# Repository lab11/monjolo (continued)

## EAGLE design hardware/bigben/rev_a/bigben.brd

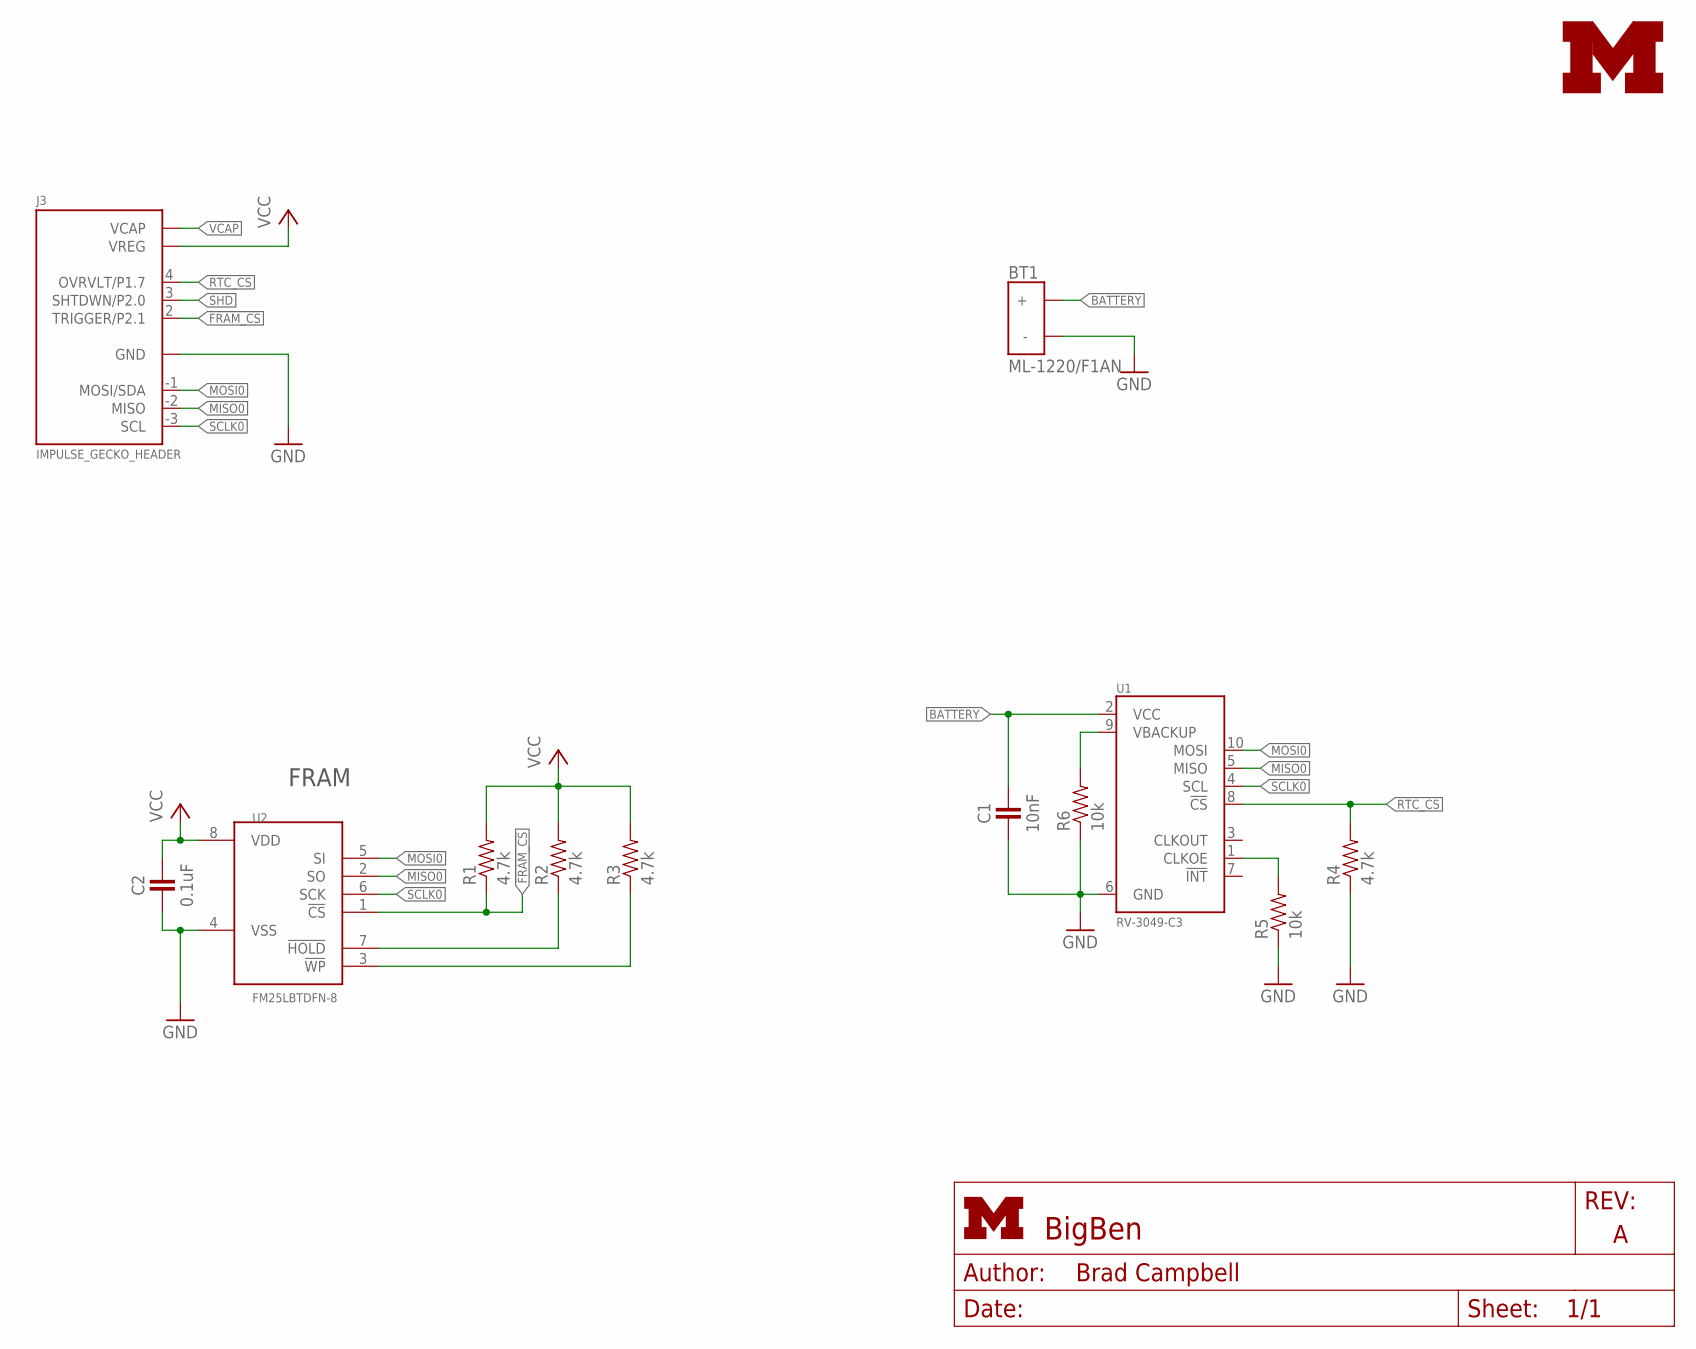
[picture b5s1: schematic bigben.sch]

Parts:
BT1: ML-1220/F1AN; ML-1220/F1BN
C1: 10nF; 0402_CAP
C2: 0.1uF; 0402_CAP
J3: IMPULSE_GECKO_HEADER; HEADER1X9/0.05IN
LOGO1: UMICH_SOLID_TINY; UMICH_SOLID_50MIL
R1, R2, R3, R4: 4.7k; 0402_RES
R5, R6: 10k; 0402_RES
U1: RV-3049-C3; MICRO-CRYSTAL-C3
U2: FM25LBTDFN-8; TDFN-8; MOUSER 877-FM25V20-DG

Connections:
!FRAM_CS: J3.2 (TRIGGER/P2.1), R1.1, U2.1 (!CS)
!FRAM_HOLD: R2.1, U2.7 (!HOLD)
!FRAM_WP: R3.1, U2.3 (!WP)
BATTERY: BT1.POS (+), C1.1, U1.2 (VCC)
GND: BT1.NEG (-), C1.2, C2.2, J3.0 (GND), R4.1, R5.1, R6.1, U1.6 (GND), U2.4 (VSS)
MISO0: J3.-2 (MISO), U1.5 (MISO), U2.2 (SO)
MOSI0: J3.-1 (MOSI/SDA), U1.10 (MOSI), U2.5 (SI)
unnamed: R6.2, U1.9 (VBACKUP)
unnamed: R5.2, U1.1 (CLKOE)
RTC_CS: J3.4 (OVRVLT/P1.7), R4.2, U1.8 (!CS)
SCLK0: J3.-3 (SCL), U1.4 (SCL), U2.6 (SCK)
SHD: J3.3 (SHTDWN/P2.0)
VCAP: J3.5 (VCAP)
VCC: C2.1, J3.1 (VREG), R1.2, R2.2, R3.2, U2.8 (VDD)

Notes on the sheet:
FRAM

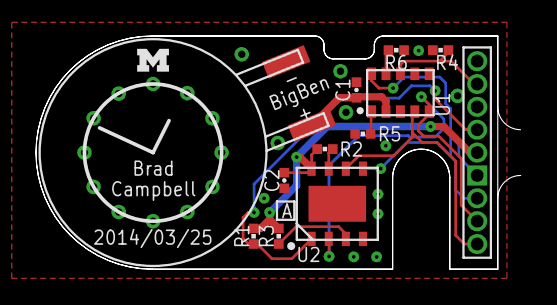
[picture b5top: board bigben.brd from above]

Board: 2 copper layers, 26.9 x 13.0 mm, 13 parts (0 on the bottom side), 12 nets.

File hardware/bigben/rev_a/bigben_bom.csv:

# Bill of Materials
# Converted from bigben_bom.xls
# Generated by bom_to_text.py

Qty,Value,Device,Package,Parts,Description,DIGIKEY,MOUSER,NEWARK
1,ML-1220/F1AN,ML-1220/F1AN,ML-1220/F1BN,BT1,BATTERY LITH 3V RECHARGE PC PINS,P663-ND,658-ML-1220/F1BN,
1,10nF,CAPACITOR,0402_CAP,C1,0402 Capacitor,445-1260-1-ND,,
1,0.1uF,CAPACITOR,0402_CAP,C2,0402 Capacitor,445-1265-1-ND,,
4,4.7k,RESISTOR,0402_RES,"R1, R2, R3, R4",Resistor,RHM4.7KCECT-ND,,
2,10k,RESISTOR,0402_RES,"R5, R6",Resistor,RHM10KCECT-ND,,
1,RV-3049-C3,RV-3049-C3,MICRO-CRYSTAL-C3,U1,The RV-3049-C3 is an ultra miniature Real-Time-Clock Module,,,RV-3049-C3
1,FM25LBTDFN-8,FM25LBTDFN-8,TDFN-8,U2,IC FRAM 4KBIT 10MHZ 8SOIC,,877-FM25V20-DG,

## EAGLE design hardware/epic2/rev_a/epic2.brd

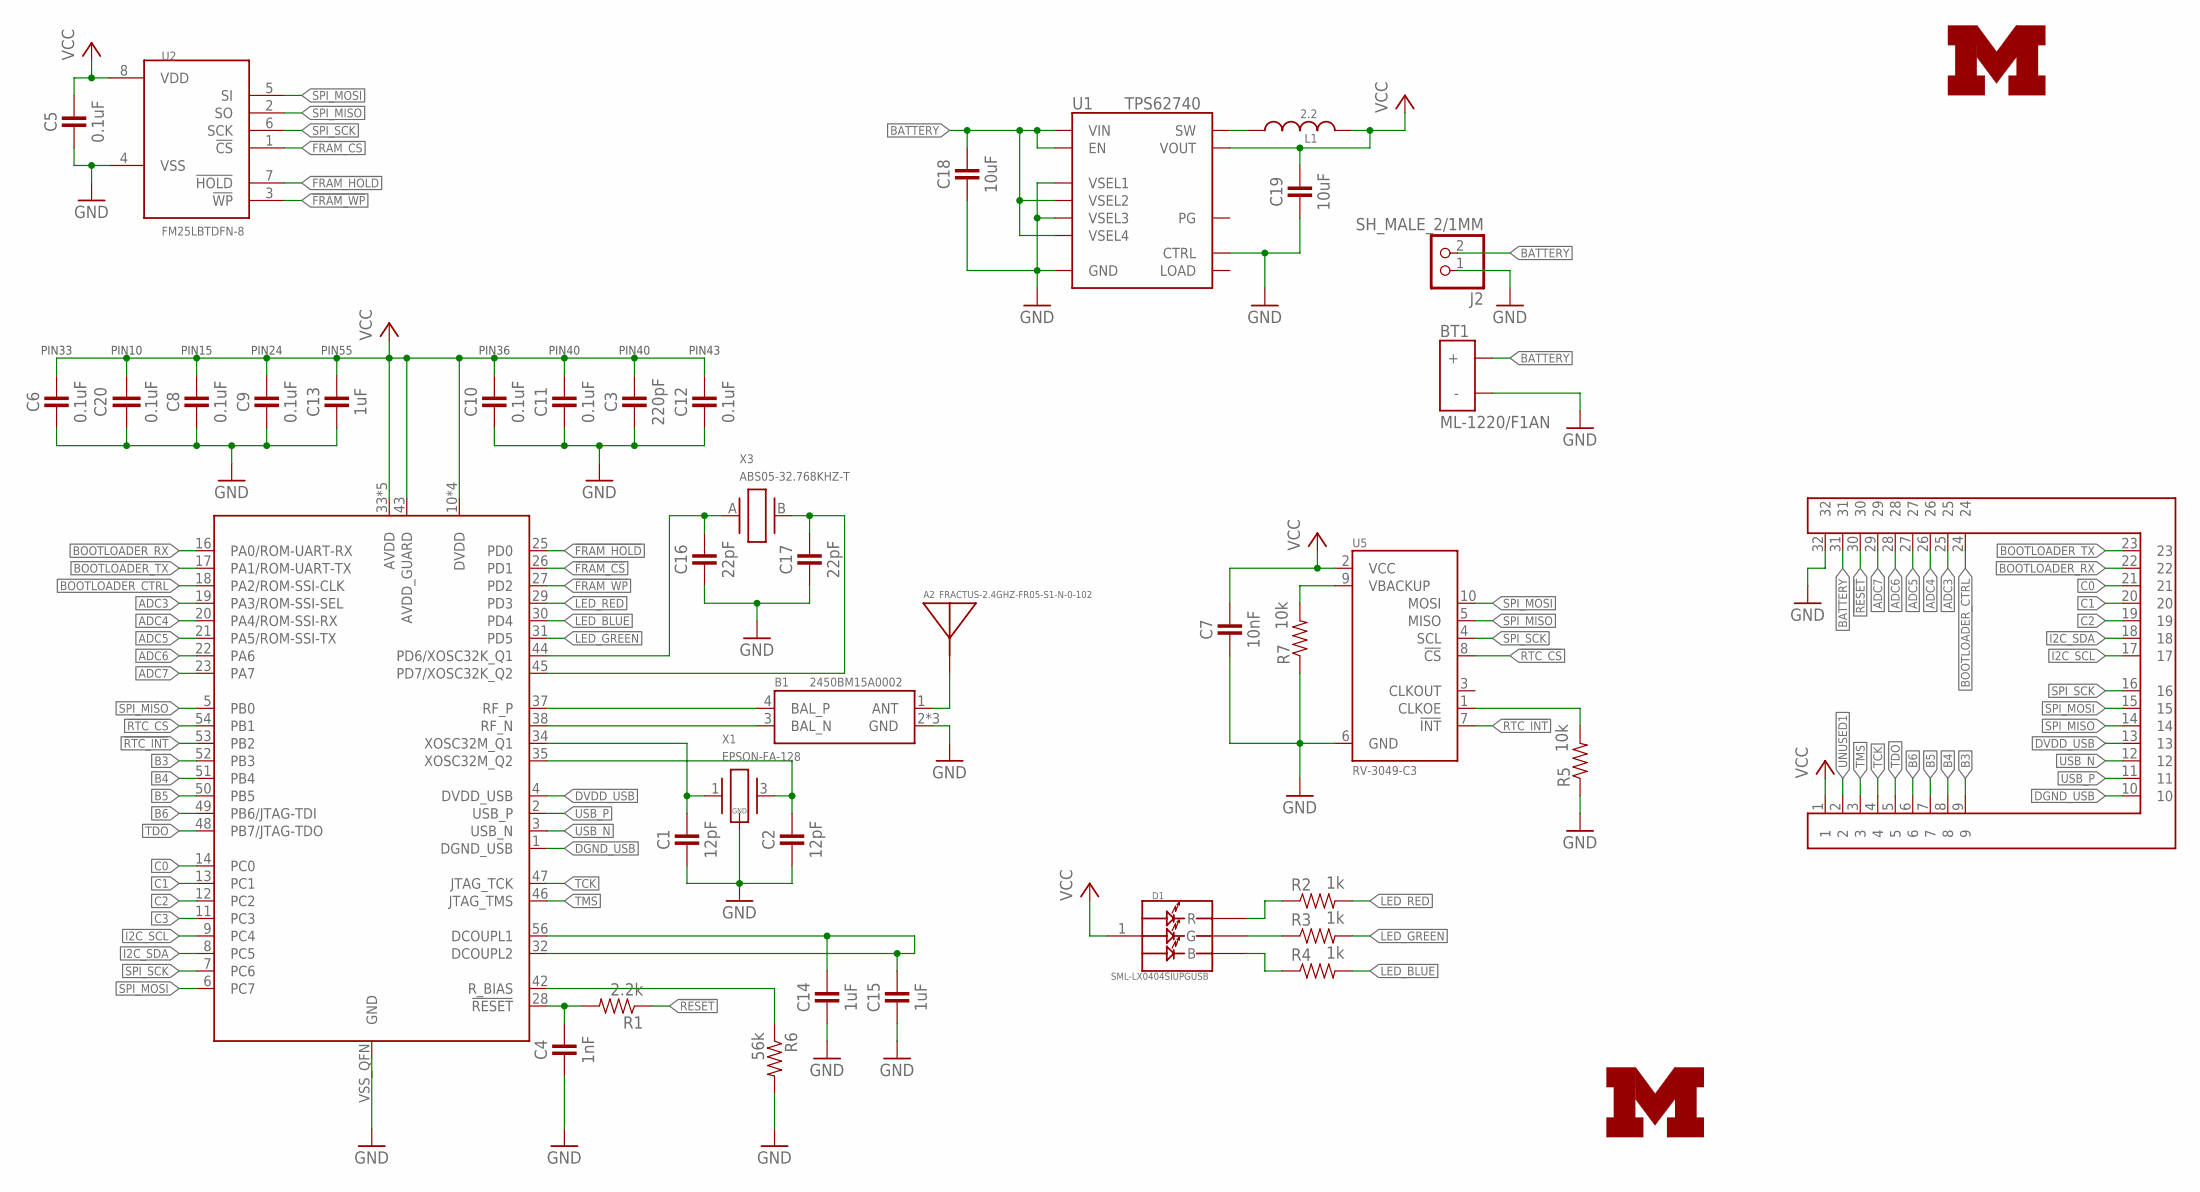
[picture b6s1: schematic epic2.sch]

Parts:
A2: FRACTUS-2.4GHZ-FR05-S1-N-0-102; FRACTUS-ANTENNA-FR05-S1-N-0-102
B1: 2450BM15A0002; 2450BM
BT1: ML-1220/F1AN; ML-1220/F1BN
C1, C2: 12pF; 0402_CAP
C3: 220pF; 0402_CAP
C4: 1nF; 0402_CAP
C5, C6, C8, C9, C10, C11, C12: 0.1uF; 0402_CAP
C7: 10nF; 0402_CAP
C13, C14, C15: 1uF; 0402_CAP
C16, C17: 22pF; 0402_CAP
C18: 10uF; 0603_CAP; DIGIKEY 490-7316-1-ND
C19: 10uF; 0603_CAP; DIGIKEY 1276-1119-1-ND
C20: 0.1uF; C0201
D1: SML-LX0404SIUPGUSB; 1MM_SQ_4PAD
J1: EPIC2-HEADER2
J2: SH_MALE_2/1MM; SH-1X2/1MM
L1: 2.2; MIPSZ201D
LOGO1: UMICH_SOLID_TINY; UMICH_SOLID_50MIL
R1: 2.2k; 0402_RES
R2, R3, R4: 1k; 0402_RES
R5, R7: 10k; 0402_RES
R6: 56k; 0402_RES
U1: TPS62740; R-PWSON-12
U2: FM25LBTDFN-8; TDFN-8; DIGIKEY FM25L04B-DGRA-ND
U3: CC2538; S-PVQFN-N56
U5: RV-3049-C3; MICRO-CRYSTAL-C3
U$1: UMICH_SOLID_SMALL; UMICH_SOLID_75MIL
X1: EPSON-FA-128; FA-128
X3: ABS05-32.768KHZ-T; ABS05

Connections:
!FRAM_CS: U2.1 (!CS), U3.26 (PD1)
!FRAM_HOLD: U2.7 (!HOLD), U3.25 (PD0)
!FRAM_WP: U2.3 (!WP), U3.27 (PD2)
!RESET: J1.30, R1.1
!RTC_CS: U3.54 (PB1), U5.8 (!CS)
!RTC_INT: U3.53 (PB2), U5.7 (!INT)
ADC3: J1.25, U3.19 (PA3/ROM-SSI-SEL)
ADC4: J1.26, U3.20 (PA4/ROM-SSI-RX)
ADC5: J1.27, U3.21 (PA5/ROM-SSI-TX)
ADC6: J1.28, U3.22 (PA6)
ADC7: J1.29, U3.23 (PA7)
ANTENNA: A2.1, B1.1 (ANT)
B3: J1.9, U3.52 (PB3)
B4: J1.8, U3.51 (PB4)
B5: J1.7, U3.50 (PB5)
B6: J1.6, U3.49 (PB6/JTAG-TDI)
BATTERY: BT1.POS (+), C18.1, J1.31, J2.2, U1.1 (VIN), U1.8 (VSEL4), U1.10 (VSEL2), U1.12 (EN)
BOOTLOADER_CTRL: J1.24, U3.18 (PA2/ROM-SSI-CLK)
BOOTLOADER_RX: J1.22, U3.16 (PA0/ROM-UART-RX)
BOOTLOADER_TX: J1.23, U3.17 (PA1/ROM-UART-TX)
C0: J1.21, U3.14 (PC0)
C1: J1.20, U3.13 (PC1)
C2: J1.19, U3.12 (PC2)
C3: U3.11 (PC3)
DGND_USB: J1.10, U3.1 (DGND_USB)
DVDD_USB: J1.13, U3.4 (DVDD_USB)
GND: B1.2 (GND), B1.5 (GND), B1.6 (GND), BT1.NEG (-), C1.2, C2.2, C3.2, C4.2, C5.2, C6.2, C7.2, C8.2, C9.2, C10.2, C11.2, C12.2, C13.2, C14.2, C15.2, C16.2, C17.2, C18.2, C19.2, C20.2, J1.32, J2.1, R5.1, R6.2, R7.1, U1.3 (GND), U1.4 (CTRL), U1.9 (VSEL3), U1.11 (VSEL1), U1.NC (GND), U2.4 (VSS), U3.VSS_QFN (GND), U5.6 (GND), X1.2 (GND), X1.4 (GND)
I2C_SCL: J1.17, U3.9 (PC4)
I2C_SDA: J1.18, U3.8 (PC5)
LED_BLUE: R4.2, U3.30 (PD4)
LED_GREEN: R3.2, U3.31 (PD5)
LED_RED: R2.2, U3.29 (PD3)
unnamed: C4.1, R1.2, U3.28 (!RESET)
unnamed: L1.1, U1.2 (SW)
unnamed: C16.1, U3.44 (PD6/XOSC32K_Q1), X3.A (1)
unnamed: D1.2 (R), R2.1
unnamed: R6.1, U3.42 (R_BIAS)
unnamed: C1.1, U3.34 (XOSC32M_Q1), X1.1
unnamed: C2.1, U3.35 (XOSC32M_Q2), X1.3 (2)
unnamed: D1.4 (G), R3.1
unnamed: D1.3 (B), R4.1
unnamed: C17.1, U3.45 (PD7/XOSC32K_Q2), X3.B (2)
unnamed: R7.2, U5.9 (VBACKUP)
unnamed: C14.1, C15.1, U3.32 (DCOUPL2), U3.56 (DCOUPL1)
unnamed: R5.2, U5.1 (CLKOE)
RF_N: B1.3 (BAL_N), U3.38 (RF_N)
RF_P: B1.4 (BAL_P), U3.37 (RF_P)
SPI_MISO: J1.14, U2.2 (SO), U3.5 (PB0), U5.5 (MISO)
SPI_MOSI: J1.15, U2.5 (SI), U3.6 (PC7), U5.10 (MOSI)
SPI_SCK: J1.16, U2.6 (SCK), U3.7 (PC6), U5.4 (SCL)
TCK: J1.4, U3.47 (JTAG_TCK)
TDO: J1.5, U3.48 (PB7/JTAG-TDO)
TMS: J1.3, U3.46 (JTAG_TMS)
UNUSED1: J1.2
USB_N: J1.12, U3.3 (USB_N)
USB_P: J1.11, U3.2 (USB_P)
VCC: C3.1, C5.1, C6.1, C7.1, C8.1, C9.1, C10.1, C11.1, C12.1, C13.1, C19.1, C20.1, D1.1 (VDD), J1.1, L1.2, U1.5 (VOUT), U2.8 (VDD), U3.10 (DVDD), U3.15 (DVDD), U3.24 (DVDD), U3.33 (AVDD), U3.36 (AVDD), U3.39 (AVDD), U3.40 (AVDD), U3.41 (AVDD), U3.43 (AVDD_GUARD), U3.55 (DVDD), U5.2 (VCC)

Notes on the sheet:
PIN10
PIN15
PIN24
PIN55
PIN33
PIN36
PIN40
PIN43

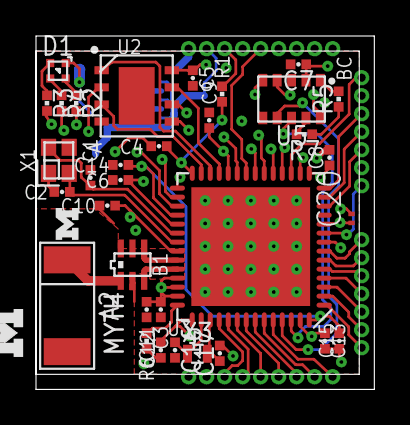
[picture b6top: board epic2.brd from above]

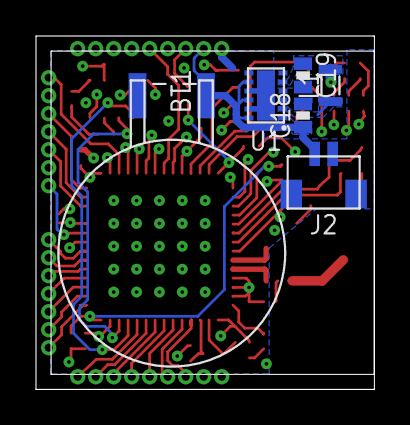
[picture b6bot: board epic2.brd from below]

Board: 4 copper layers, 18.8 x 19.6 mm, 42 parts (6 on the bottom side), 55 nets.

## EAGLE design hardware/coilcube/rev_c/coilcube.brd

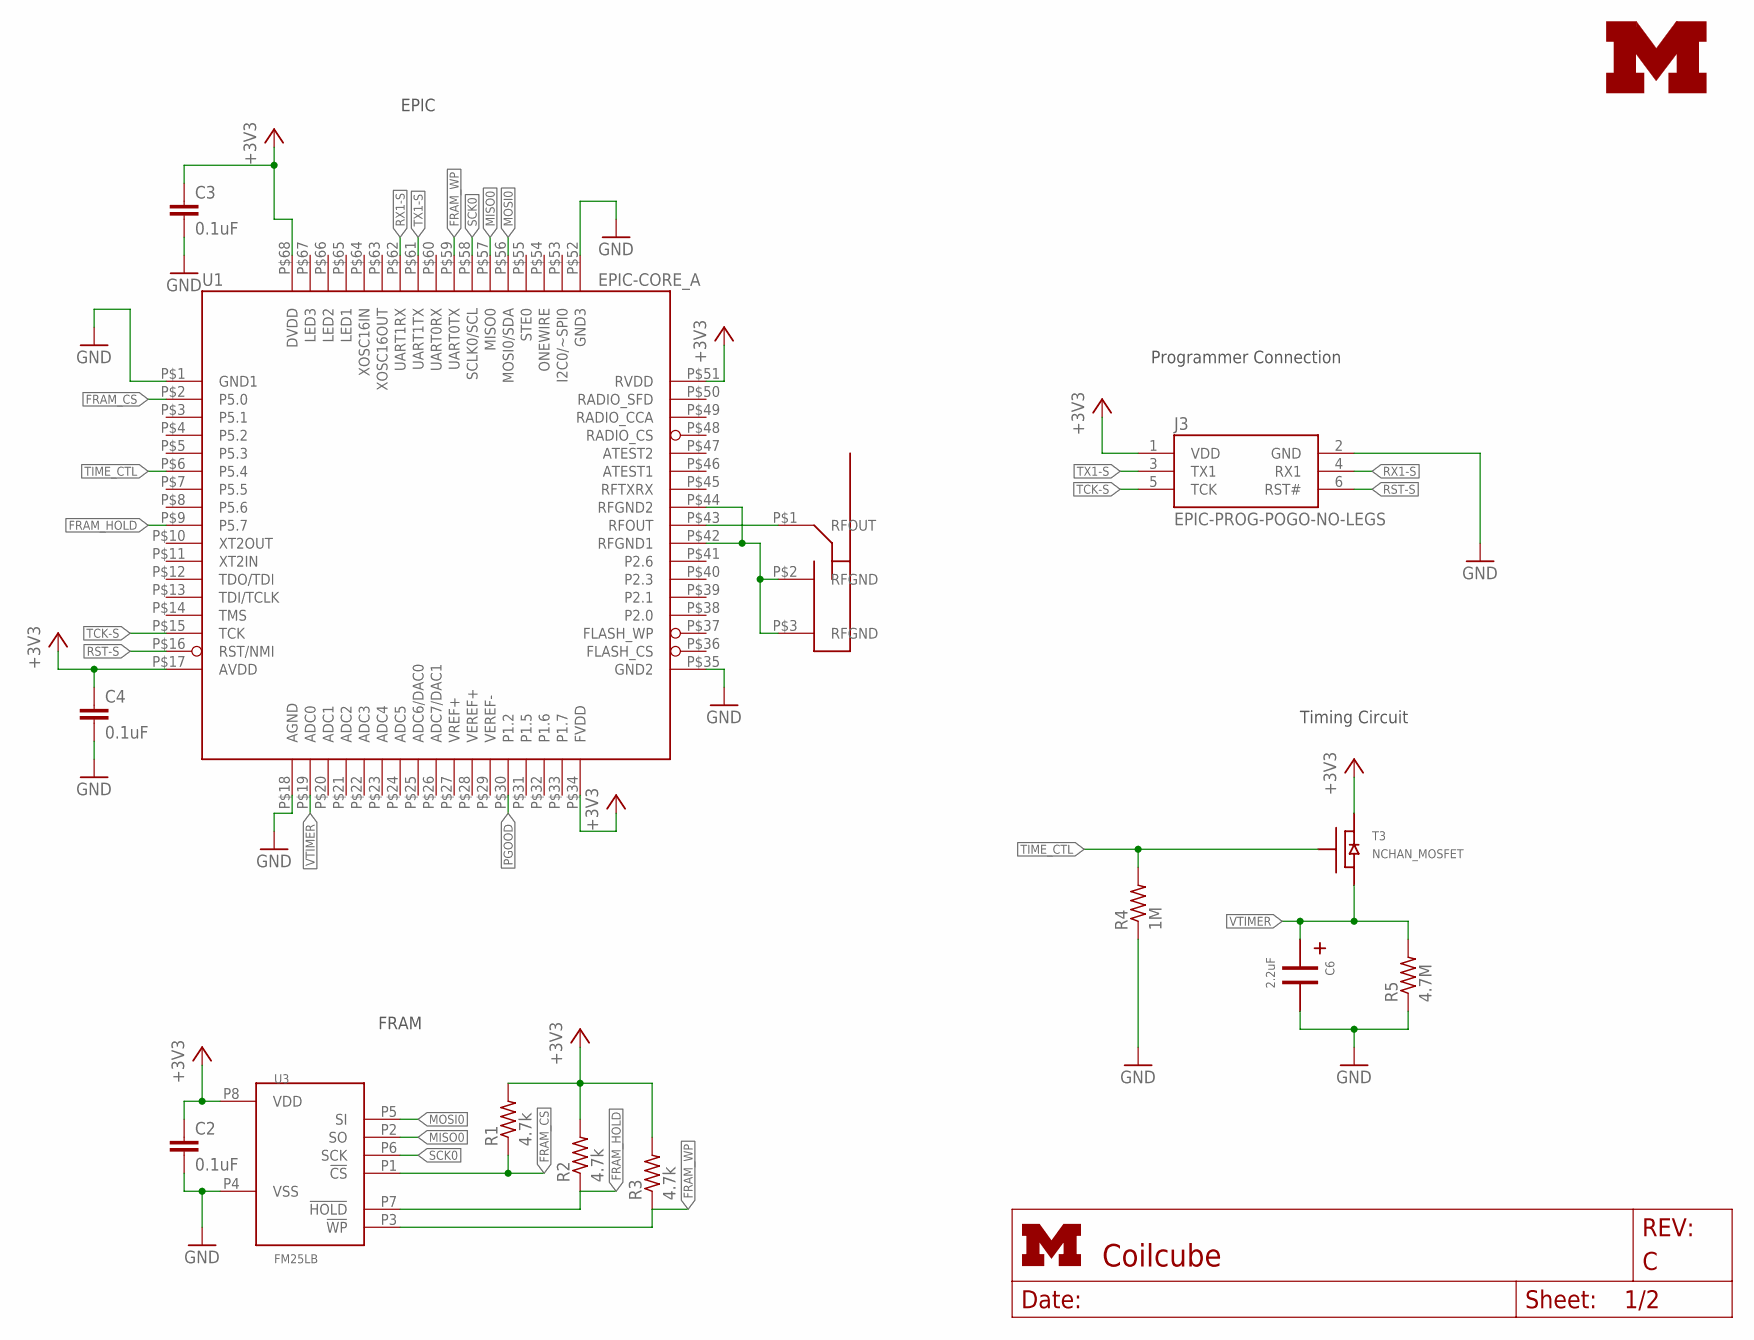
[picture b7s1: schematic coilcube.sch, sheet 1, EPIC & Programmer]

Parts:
ANT1: PIFA-2.4GHZ
C2, C3, C4: 0.1uF; C0603; DIGIKEY 445-1316-1-ND
C6: 2.2uF; CPOL_EEA_1MM5
J3: EPIC-PROG-POGO-NO-LEGS; TC2030-IDC-NL
R1, R2, R3: 4.7k; R0603; DIGIKEY P4.7KGCT-ND
R4: 1M; R0603; DIGIKEY RHM1.00MCFCT-ND
R5: 4.7M; R0603; DIGIKEY RHM4.7MCGDKR-ND
T3: NCHAN_MOSFET; DIGIKEY 568-3244-1-ND
U1: EPIC-CORE_A; EPIC-LCC68
U3: FM25LB; SOIC_8; DIGIKEY 428-3210-ND
U$1: UMICH_SOLID_MEDIUM; UMICH_SOLID_200MIL

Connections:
+3V3: C2.1, C3.1, C4.1, J3.1 (VDD), R1.2, R2.2, R3.2, T3.D, U1.P$17 (AVDD), U1.P$34 (FVDD), U1.P$51 (RVDD), U1.P$68 (DVDD), U3.P8 (VDD); also elsewhere on the board
FRAM_CS: R1.1, U1.P$2 (P5.0), U3.P1 (!CS)
FRAM_HOLD: R2.1, U1.P$9 (P5.7), U3.P7 (!HOLD)
FRAM_WP: R3.1, U1.P$59 (UART0TX), U3.P3 (!WP)
GND: C2.2, C3.2, C4.2, C6.-, J3.2 (GND), R4.1, R5.1, U1.P$1 (GND1), U1.P$18 (AGND), U1.P$35 (GND2), U1.P$52 (GND3), U3.P4 (VSS); also elsewhere on the board
MISO0: U1.P$57 (MISO0), U3.P2 (SO)
MOSI0: U1.P$56 (MOSI0/SDA), U3.P5 (SI)
unnamed: ANT1.P$1 (RFOUT), U1.P$43 (RFOUT)
PGOOD: U1.P$30 (P1.2); also elsewhere on the board
RFGND: ANT1.P$2 (RFGND), ANT1.P$3 (RFGND), U1.P$42 (RFGND1), U1.P$44 (RFGND2)
RST-S: J3.6 (RST#), U1.P$16 (RST/NMI)
RX1-S: J3.4 (RX1), U1.P$62 (UART1RX)
SCK0: U1.P$58 (SCLK0/SCL), U3.P6 (SCK)
TCK-S: J3.5 (TCK), U1.P$15 (TCK)
TIME_CTL: R4.2, T3.G, U1.P$6 (P5.4)
TX1-S: J3.3 (TX1), U1.P$61 (UART1TX)
VTIMER: C6.+, R5.2, T3.S, U1.P$19 (ADC0)

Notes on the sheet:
Programmer Connection
EPIC
FRAM
Timing Circuit

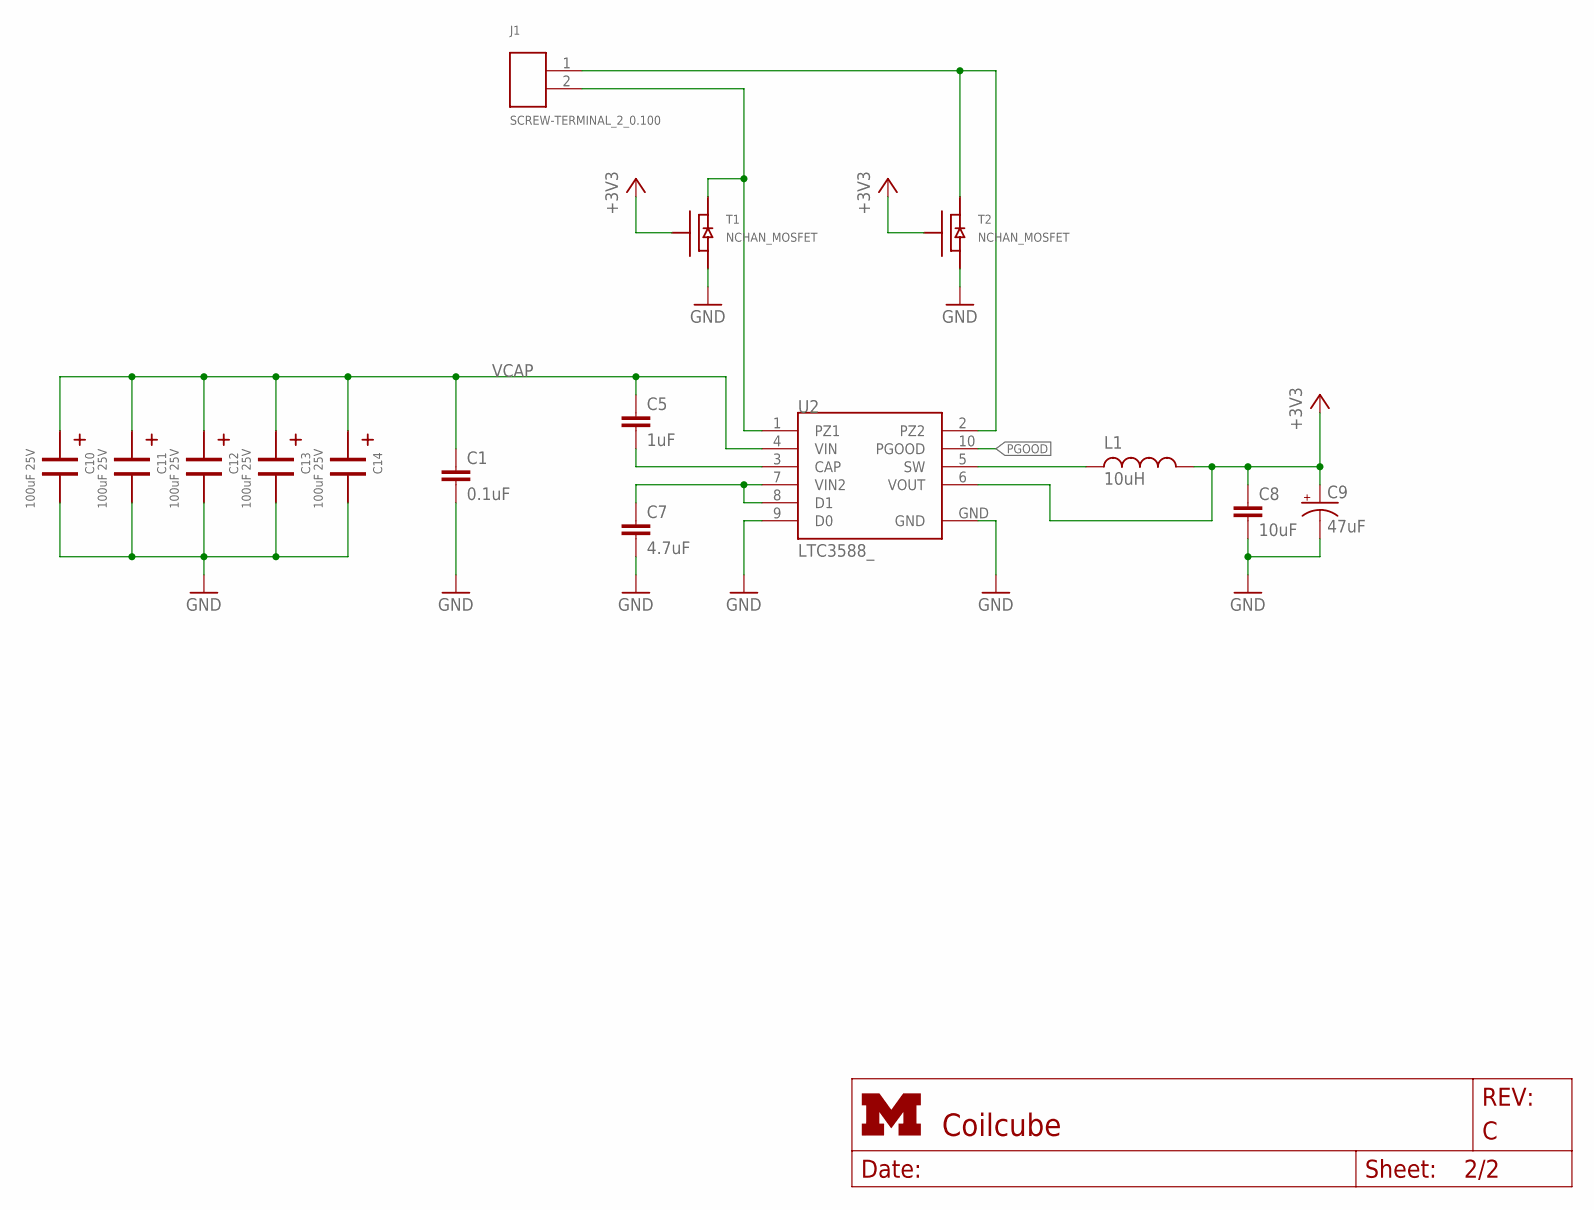
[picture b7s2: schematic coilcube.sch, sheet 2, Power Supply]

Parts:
C1: 0.1uF; C0603; DIGIKEY 445-1316-1-ND
C5: 1uF; C0603; DIGIKEY 445-1321-1-ND
C7: 4.7uF; C0603; DIGIKEY 445-5178-1-ND
C8: 10uF; C1206; DIGIKEY 399-8152-1-ND
C9: 47uF; EIA3216; DIGIKEY 399-3700-1-ND
C10, C11, C12, C13, C14: 100uF 25V; 2917_CAP_POL; DIGIKEY 399-5175-1-ND
J1: SCREW-TERMINAL_2_0.100; CONN_BLOCK_2
L1: 10uH; 1210; DIGIKEY 587-1625-1-ND
T1, T2: NCHAN_MOSFET; DIGIKEY SI1302DL-T1-GE3CT-ND
U2: LTC3588_; MSOP-10-GNDPAD; DIGIKEY LTC3588EMSE-1#PBF-ND

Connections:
+3V3: C8.1, C9.A (+), L1.2, T1.G, T2.G, U2.6 (VOUT); also elsewhere on the board
GND: C1.2, C7.2, C8.2, C9.C (-), C10.-, C11.-, C12.-, C13.-, C14.-, T1.S, T2.S, U2.9 (D0), U2.GND; also elsewhere on the board
unnamed: L1.1, U2.5 (SW)
unnamed: C5.2, U2.3 (CAP)
PGOOD: U2.10 (PGOOD); also elsewhere on the board
PZ1: J1.2, T1.D, U2.1 (PZ1)
PZ2: J1.1, T2.D, U2.2 (PZ2)
VCAP: C1.1, C5.1, C10.+, C11.+, C12.+, C13.+, C14.+, U2.4 (VIN)
VIN2: C7.1, U2.7 (VIN2), U2.8 (D1)

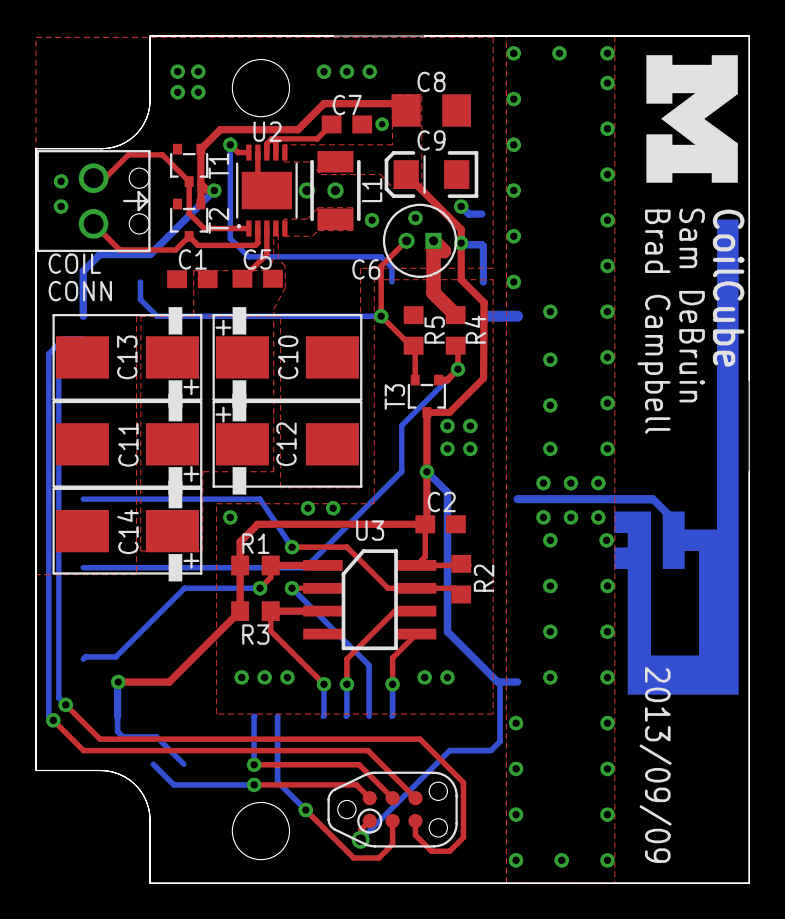
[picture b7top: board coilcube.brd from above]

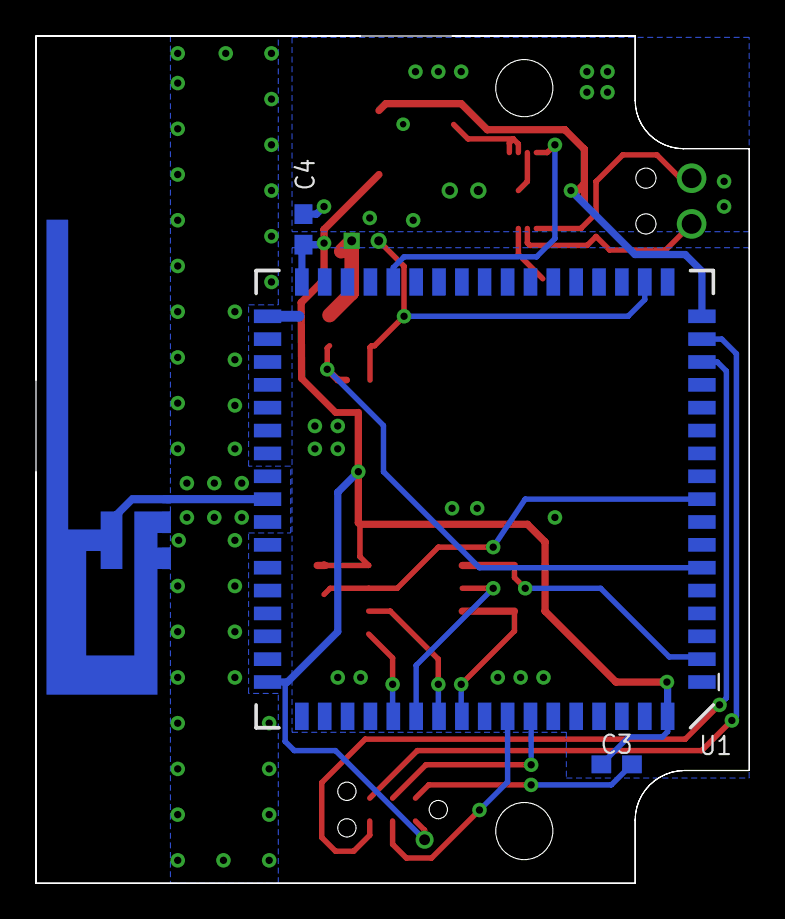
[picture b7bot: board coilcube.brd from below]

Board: 2 copper layers, 39.6 x 47.1 mm, 30 parts (4 on the bottom side), 23 nets.

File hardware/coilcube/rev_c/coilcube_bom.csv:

# Bill of Materials
# Converted from coilcube_bom.xlsx
# Generated by bom_to_text.py

Qty,Value,Device,Package,Parts,Description,DIGIKEY,DIGIREEL,Notes
4,0.1uF,C-EUC0603,C0603,"C1, C2, C3, C4","CAPACITOR, European symbol",445-1316-1-ND,445-1316-6-ND,
1,1uF,C-EUC0603,C0603,C5,"CAPACITOR, European symbol",445-1321-1-ND,445-1321-6-ND,
1,2.2uF,CAP_POLEA1MM5,CPOL_EEA_1MM5,C6,,P14506-ND,,
1,4.7uF,C-EUC0603,C0603,C7,"CAPACITOR, European symbol",445-5178-1-ND,445-5178-6-ND,
1,10uF,C-EUC1206,C1206,C8,"CAPACITOR, European symbol",399-8152-1-ND,399-8152-6-ND,
1,47uF,CAP_POL1206,EIA3216,C9,Capacitor Polarized,399-3700-1-ND,399-3700-6-ND,
5,100uF 25V,2917_CAP_POL,2917_CAP_POL,"C10, C11, C12, C13, C14",,399-5175-1-ND,399-5175-6-ND,Replacement: 399-8410-1-ND
1,SCREW-TERMINAL_2_0.100,SCREW-TERMINAL_2_0.100,CONN_BLOCK_2,J1,2x 0.100 in screw terminal block,277-1273-ND,,
1,10uH,INDUCTOR1210,1210,L1,Inductors,587-1625-1-ND,587-1625-6-ND,
3,4.7k,R-US_R0603,R0603,"R1, R2, R3","RESISTOR, American symbol",P4.7KGCT-ND,P4.7KGDKR-ND,
1,1M,R-US_R0603,R0603,R4,"RESISTOR, American symbol",RHM1.00MCFCT-ND,RHM1.00MCFDKR-ND,
1,4.7M,R-US_R0603,R0603,R5,"RESISTOR, American symbol",RHM4.7MCGCT-ND,RHM4.7MCGDKR-ND,
2,NCHAN_MOSFET,NCHAN_MOSFET,NCHAN_MOSFET,"T1, T2",,SI1302DL-T1-GE3CT-ND,SI1302DL-T1-GE3DKR-ND,
1,NCHAN_MOSFET,NCHAN_MOSFET,NCHAN_MOSFET,T3,,568-3244-1-ND,568-3244-6-ND,
1,EPIC-CORE_A,EPIC-CORE_A,EPIC-LCC68,U1,,,,Customer provided.
1,LTC3588_,LTC3588_,MSOP-10-GNDPAD,U2,Energy Harvesting Power Supply,LTC3588EMSE-1#PBF-ND,,
1,FM25LB,FM25LB,SOIC_8,U3,,428-3210-ND,,

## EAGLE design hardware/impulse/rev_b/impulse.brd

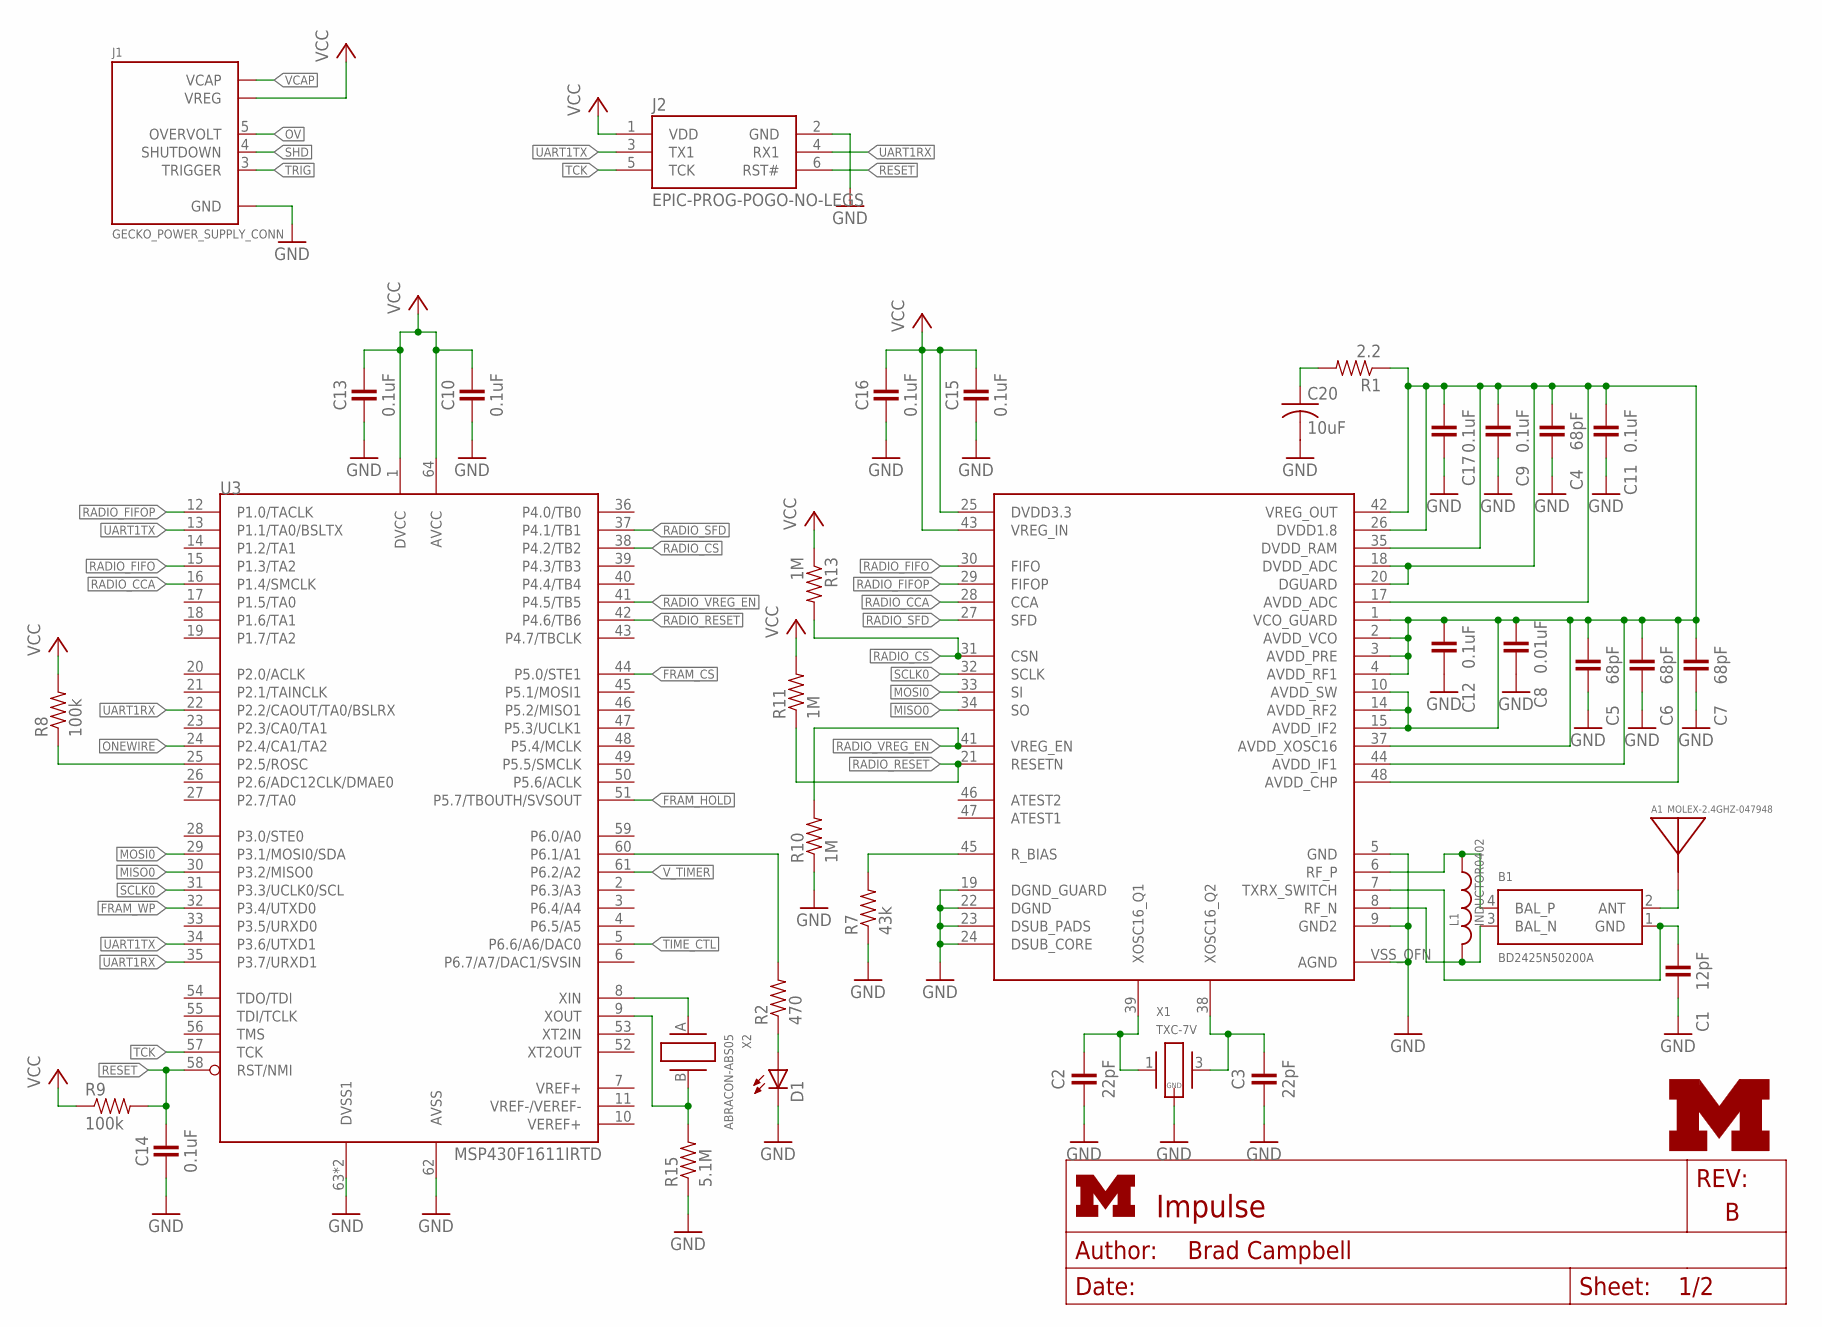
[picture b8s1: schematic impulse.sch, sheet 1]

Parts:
A1: MOLEX-2.4GHZ-047948; MOLEX-47948-ANTENNA
B1: BD2425N50200A
C1: 12pF; 0402_CAP
C2, C3: 22pF; 0402_CAP
C4, C5, C6, C7: 68pF; 0402_CAP
C8: 0.01uF; 0402_CAP
C9, C10, C11, C12, C13, C14, C15, C16, C17: 0.1uF; 0402_CAP
C20: 10uF; C0805; DIGIKEY 478-2561-1-ND
D1: LED0603; LED-0603
J1: GECKO_POWER_SUPPLY_CONN; HEADER1X6/0.05IN
J2: EPIC-PROG-POGO-NO-LEGS; TC2030-IDC-NL
L1: INDUCTOR0402; 0402_CAP; DIGIKEY 712-1419-1-ND
R1: 2.2; 0402_RES
R2: 470; 0402_RES
R7: 43k; 0402_RES
R8, R9: 100k; 0402_RES
R10, R11, R13: 1M; 0402_RES
R15: 5.1M; 0402_RES
U3: MSP430F1611IRTD; S-PVQFN-N64
U4: CC2420RGZ; S-PVQFN-N48
U$1: UMICH_SOLID_SMALL; UMICH_SOLID_75MIL
X1: TXC-7V
X2: ABRACON-ABS05; ABS05

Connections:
!FRAM_CS: U3.44 (P5.0/STE1); also elsewhere on the board
!FRAM_HOLD: U3.51 (P5.7/TBOUTH/SVSOUT); also elsewhere on the board
!FRAM_WP: U3.32 (P3.4/UTXD0); also elsewhere on the board
!RADIO_CS: R13.2, U3.38 (P4.2/TB2), U4.31 (CSN)
!RADIO_RESET: R11.1, U3.42 (P4.6/TB6), U4.21 (RESETN)
!RESET: C14.1, J2.6 (RST#), R9.2, U3.58 (RST/NMI)
GND: C1.2, C2.2, C3.2, C4.2, C5.2, C6.2, C7.2, C8.2, C9.2, C10.2, C11.2, C12.2, C13.2, C14.2, C15.2, C16.2, C17.2, C20.2, D1.C, J1.1 (GND), J2.2 (GND), R7.1, R10.1, R15.1, U3.62 (AVSS), U3.63 (DVSS1), U3.GND (DVSS1), U4.5 (GND), U4.9 (GND2), U4.19 (DGND_GUARD), U4.22 (DGND), U4.23 (DSUB_PADS), U4.24 (DSUB_CORE), U4.VSS_QFN (AGND), X1.2 (GND), X1.4 (GND); also elsewhere on the board
MISO0: U3.30 (P3.2/MISO0), U4.34 (SO); also elsewhere on the board
MOSI0: U3.29 (P3.1/MOSI0/SDA), U4.33 (SI); also elsewhere on the board
unnamed: R8.1, U3.25 (P2.5/ROSC)
unnamed: R7.2, U4.45 (R_BIAS)
unnamed: D1.A, R2.1
unnamed: C20.1, R1.2
unnamed: C4.1, C5.1, C6.1, C7.1, C8.1, C9.1, C11.1, C12.1, C17.1, R1.1, U4.1 (VCO_GUARD), U4.2 (AVDD_VCO), U4.3 (AVDD_PRE), U4.4 (AVDD_RF1), U4.10 (AVDD_SW), U4.14 (AVDD_RF2), U4.15 (AVDD_IF2), U4.17 (AVDD_ADC), U4.18 (DVDD_ADC), U4.20 (DGUARD), U4.26 (DVDD1.8), U4.35 (DVDD_RAM), U4.37 (AVDD_XOSC16), U4.42 (VREG_OUT), U4.44 (AVDD_IF1), U4.48 (AVDD_CHP)
unnamed: U3.8 (XIN), X2.A (1)
unnamed: R2.2, U3.60 (P6.1/A1)
unnamed: R15.2, U3.9 (XOUT), X2.B (2)
unnamed: B1.1 (GND), C1.1, U4.7 (TXRX_SWITCH)
unnamed: B1.3 (BAL_N), L1.2, U4.8 (RF_N)
unnamed: B1.4 (BAL_P), L1.1, U4.6 (RF_P)
unnamed: C3.1, U4.38 (XOSC16_Q2), X1.3 (2)
unnamed: C2.1, U4.39 (XOSC16_Q1), X1.1
ONEWIRE: U3.24 (P2.4/CA1/TA2); also elsewhere on the board
OV: J1.5 (OVERVOLT)
RADIO_CCA: U3.16 (P1.4/SMCLK), U4.28 (CCA)
RADIO_FIFO: U3.15 (P1.3/TA2), U4.30 (FIFO)
RADIO_FIFOP: U3.12 (P1.0/TACLK), U4.29 (FIFOP)
RADIO_SFD: U3.37 (P4.1/TB1), U4.27 (SFD)
RADIO_VREG_EN: R10.2, U3.41 (P4.5/TB5), U4.41 (VREG_EN)
SCLK0: U3.31 (P3.3/UCLK0/SCL), U4.32 (SCLK); also elsewhere on the board
SHD: J1.4 (SHUTDOWN)
TCK: J2.5 (TCK), U3.57 (TCK)
TIME_CTL: U3.5 (P6.6/A6/DAC0); also elsewhere on the board
TRIG: J1.3 (TRIGGER)
UART1RX: J2.4 (RX1), U3.22 (P2.2/CAOUT/TA0/BSLRX), U3.35 (P3.7/URXD1)
UART1TX: J2.3 (TX1), U3.13 (P1.1/TA0/BSLTX), U3.34 (P3.6/UTXD1)
UNBAL: A1.1, B1.2 (ANT)
VCAP: J1.6 (VCAP)
VCC: C10.1, C13.1, C15.1, C16.1, J1.2 (VREG), J2.1 (VDD), R8.2, R9.1, R11.2, R13.1, U3.1 (DVCC), U3.64 (AVCC), U4.25 (DVDD3.3), U4.43 (VREG_IN); also elsewhere on the board
V_TIMER: U3.61 (P6.2/A2); also elsewhere on the board
